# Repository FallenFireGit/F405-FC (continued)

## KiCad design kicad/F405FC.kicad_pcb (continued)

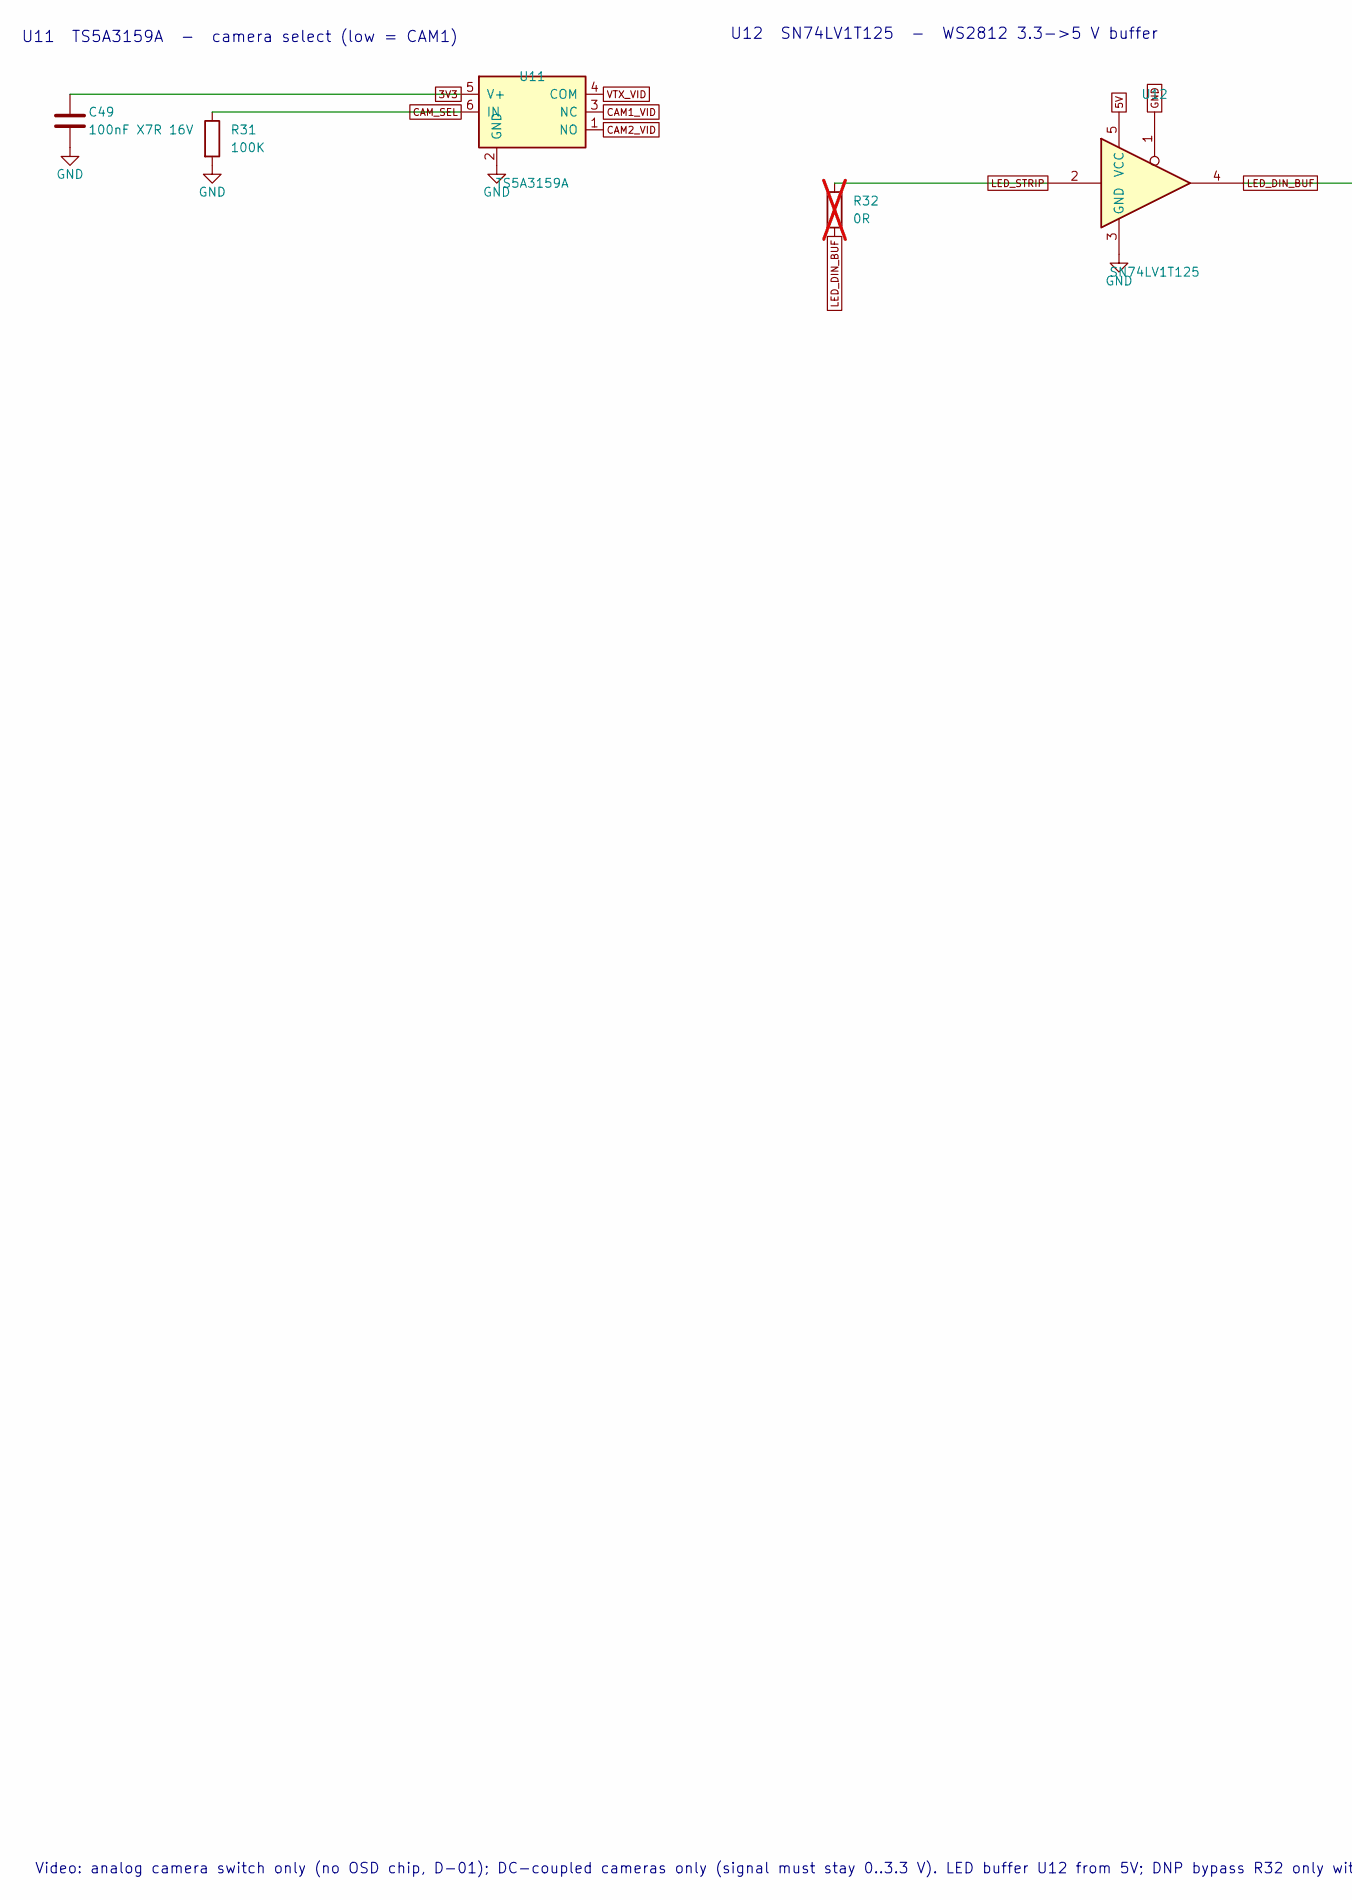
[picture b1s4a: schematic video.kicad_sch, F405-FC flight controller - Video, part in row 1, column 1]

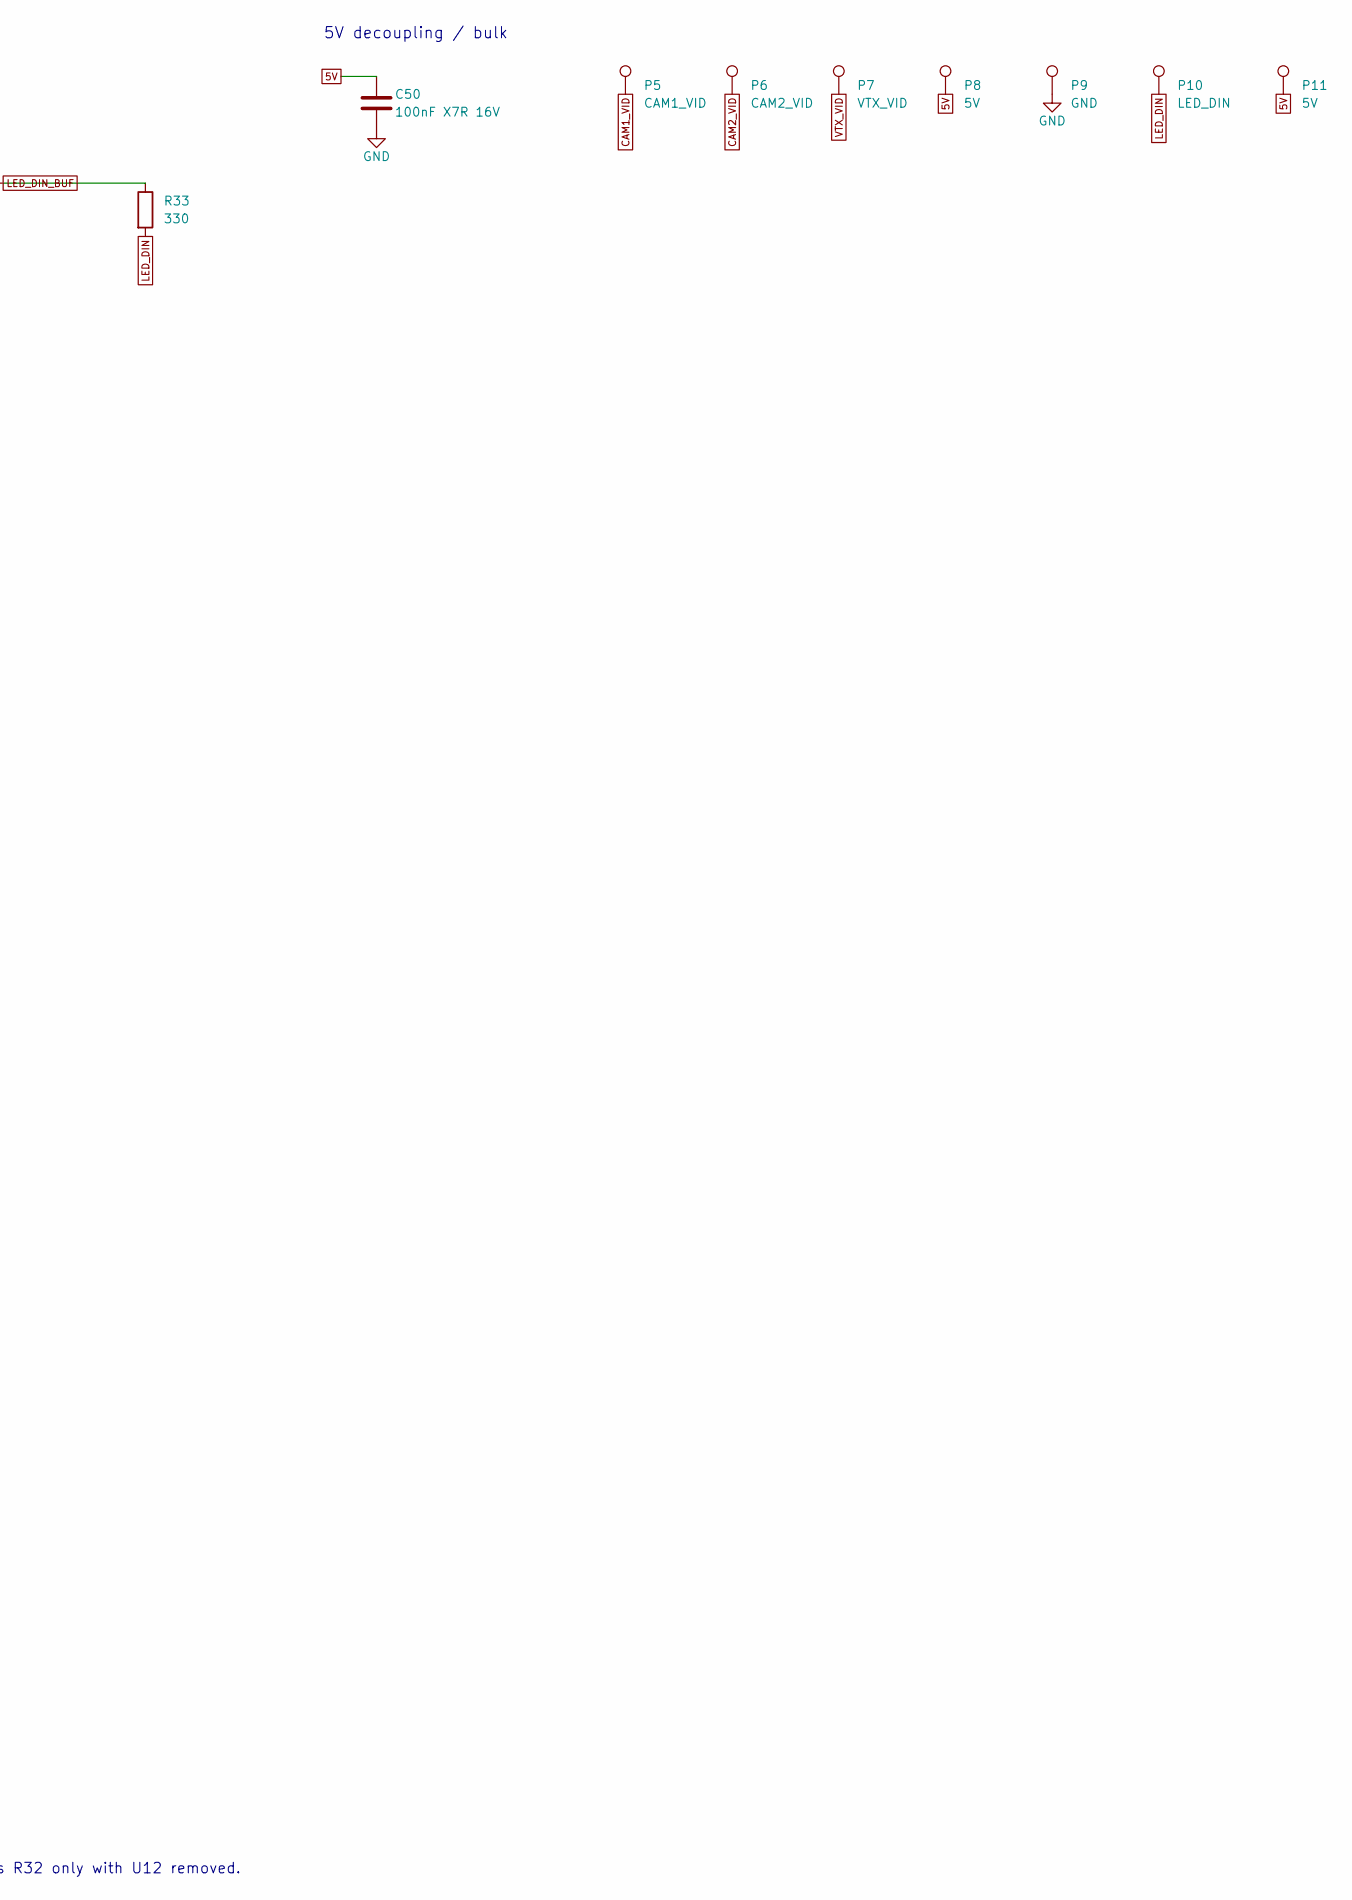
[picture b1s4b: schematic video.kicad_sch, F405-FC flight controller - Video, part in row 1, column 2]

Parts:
C49, C50: 100nF X7R 16V; C_0402_1005Metric; MPN CL05B104KO5NNNC; DigiKey 1276-1001-1-ND
P5: CAM1_VID; Pad_SMD_1.2x1.6mm; MPN n/a (PCB pad); DigiKey n/a (PCB pad)
P6: CAM2_VID; Pad_SMD_1.2x1.6mm; MPN n/a (PCB pad); DigiKey n/a (PCB pad)
P7: VTX_VID; Pad_SMD_1.2x1.6mm; MPN n/a (PCB pad); DigiKey n/a (PCB pad)
P8: 5V; Pad_SMD_1.2x1.6mm; MPN n/a (PCB pad); DigiKey n/a (PCB pad)
P9: GND; Pad_SMD_1.2x1.6mm; MPN n/a (PCB pad); DigiKey n/a (PCB pad)
P10: LED_DIN; Pad_SMD_1.2x1.6mm; MPN n/a (PCB pad); DigiKey n/a (PCB pad)
P11: 5V; Pad_SMD_1.5x2.0mm; MPN n/a (PCB pad); DigiKey n/a (PCB pad)
R31: 100K; R_0402_1005Metric; MPN RC0402FR-07100KL; DigiKey 311-100KLRCT-ND
R32: 0R; R_0402_1005Metric; MPN RC0402JR-070RL; DigiKey 311-0.0JRCT-ND; not fitted
R33: 330; R_0402_1005Metric; MPN RC0402FR-07330RL; DigiKey 311-330LRCT-ND
U11: TS5A3159A; SOT-23-6; MPN TS5A3159ADBVR; DigiKey 296-19265-1-ND
U12: SN74LV1T125; SOT-23-5; MPN SN74LV1T125DBVR; DigiKey 296-37172-1-ND

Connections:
3V3: C49.1, U11.5 (V+); also elsewhere on the board
5V: C50.1, P8.1, P11.1, U12.5 (VCC); also elsewhere on the board
CAM1_VID: P5.1, U11.3 (NC)
CAM2_VID: P6.1, U11.1 (NO)
CAM_SEL: R31.1, U11.6 (IN); also elsewhere on the board
GND: C49.2, C50.2, P9.1, R31.2, U11.2 (GND), U12.1, U12.3 (GND); also elsewhere on the board
LED_DIN: P10.1, R33.2
LED_DIN_BUF: R32.2, R33.1, U12.4
LED_STRIP: R32.1, U12.2; also elsewhere on the board
VTX_VID: P7.1, U11.4 (COM)

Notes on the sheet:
U11 TS5A3159A - camera select (low = CAM1)
U12 SN74LV1T125 - WS2812 3.3->5 V buffer
5V decoupling / bulk
Video: analog camera switch only (no OSD chip, D-01); DC-coupled cameras only (signal must stay 0..3.3 V). LED buffer U12 from 5V; DNP bypass R32 only with U12 removed.

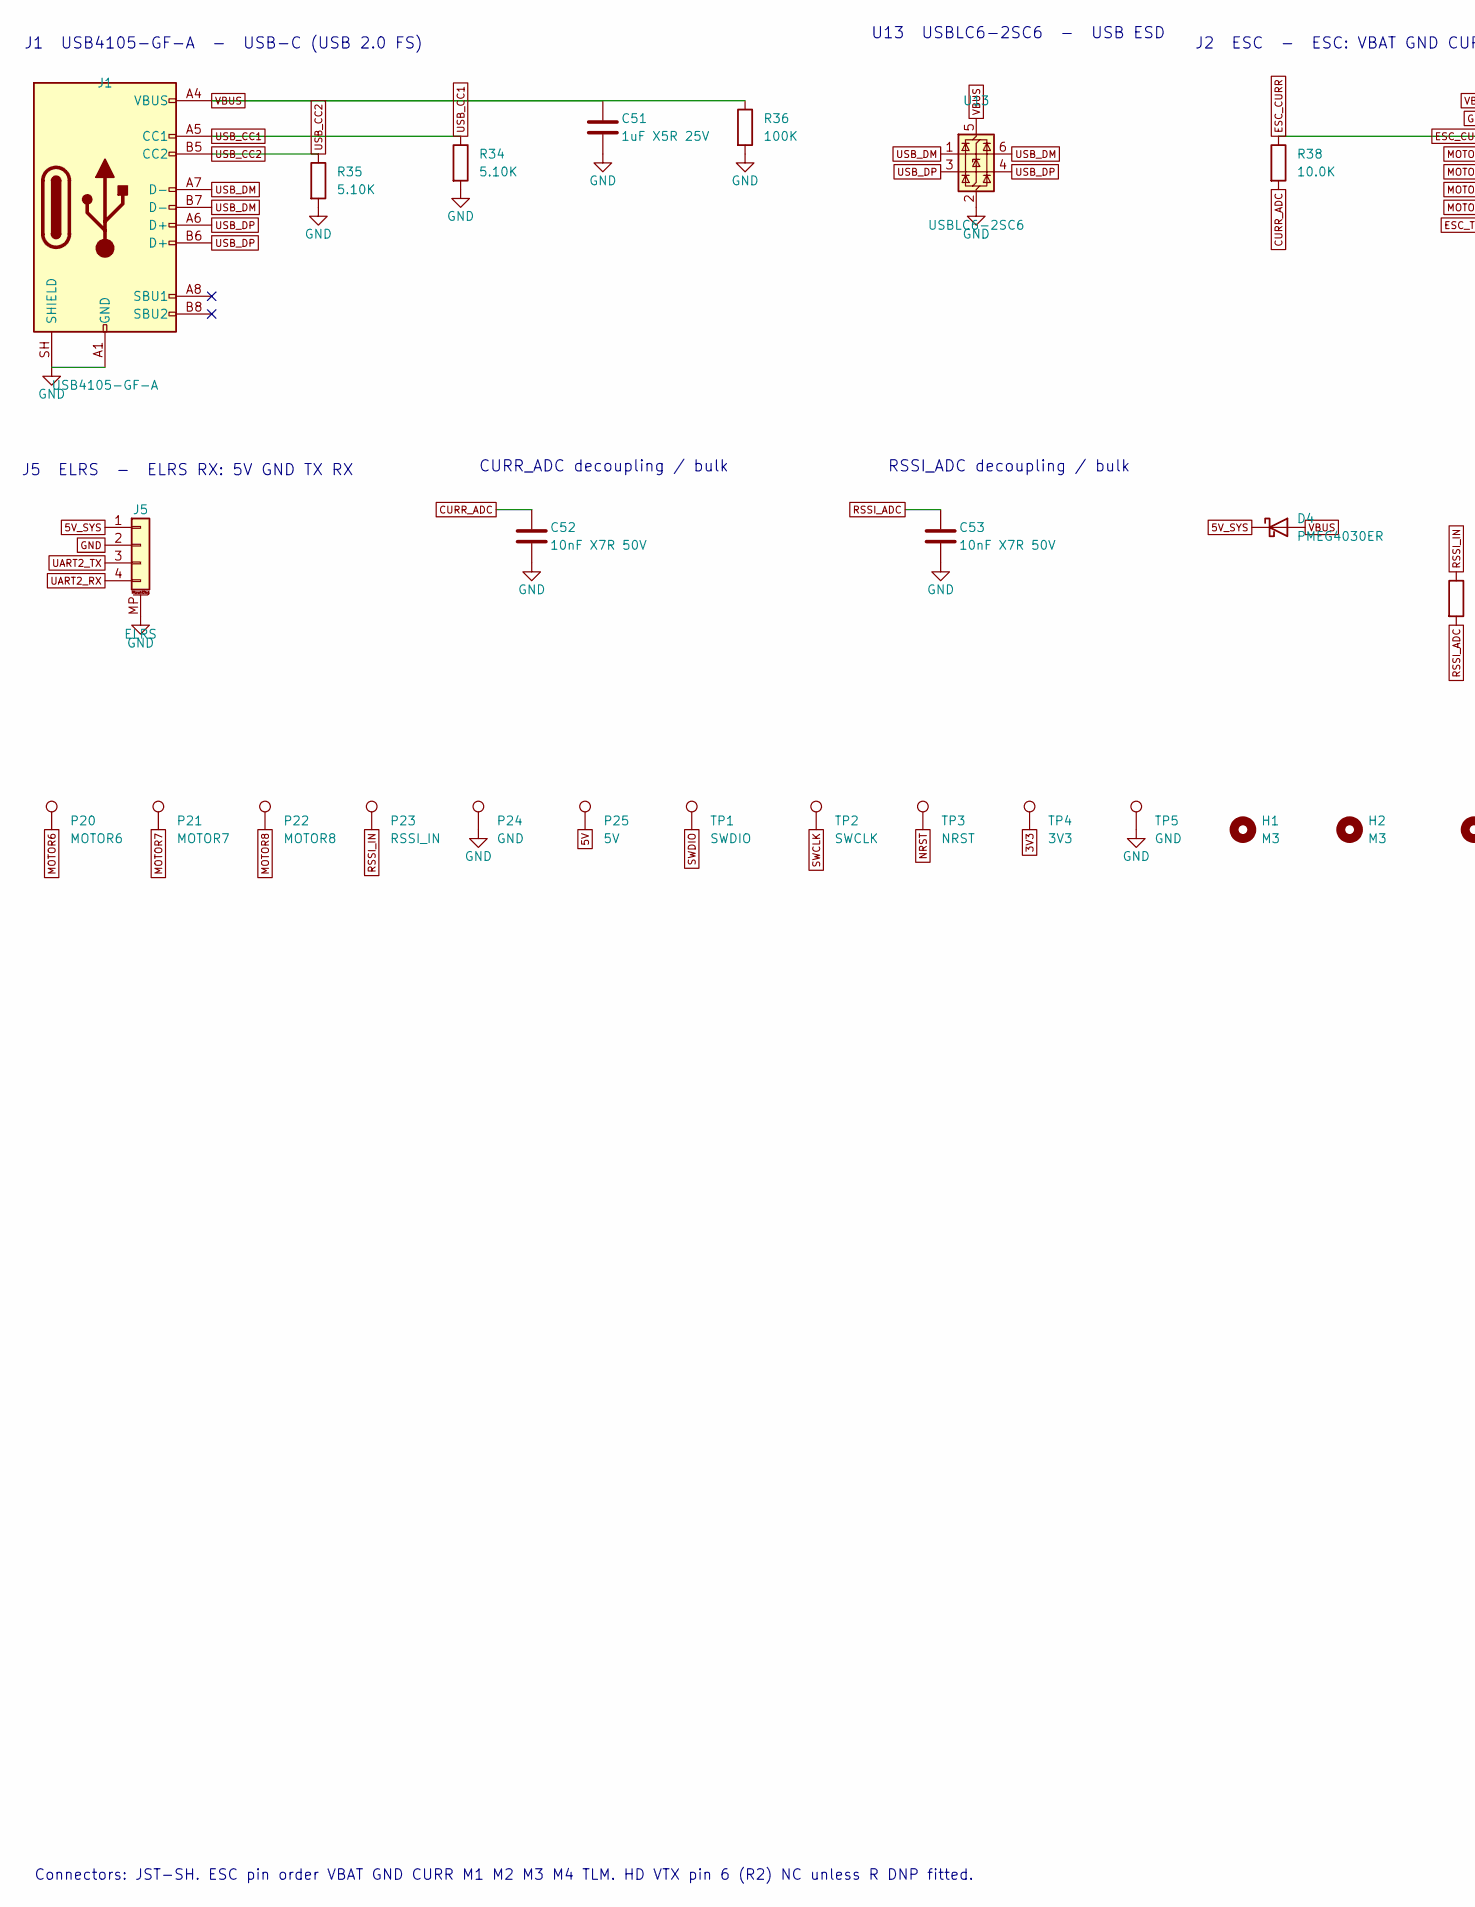
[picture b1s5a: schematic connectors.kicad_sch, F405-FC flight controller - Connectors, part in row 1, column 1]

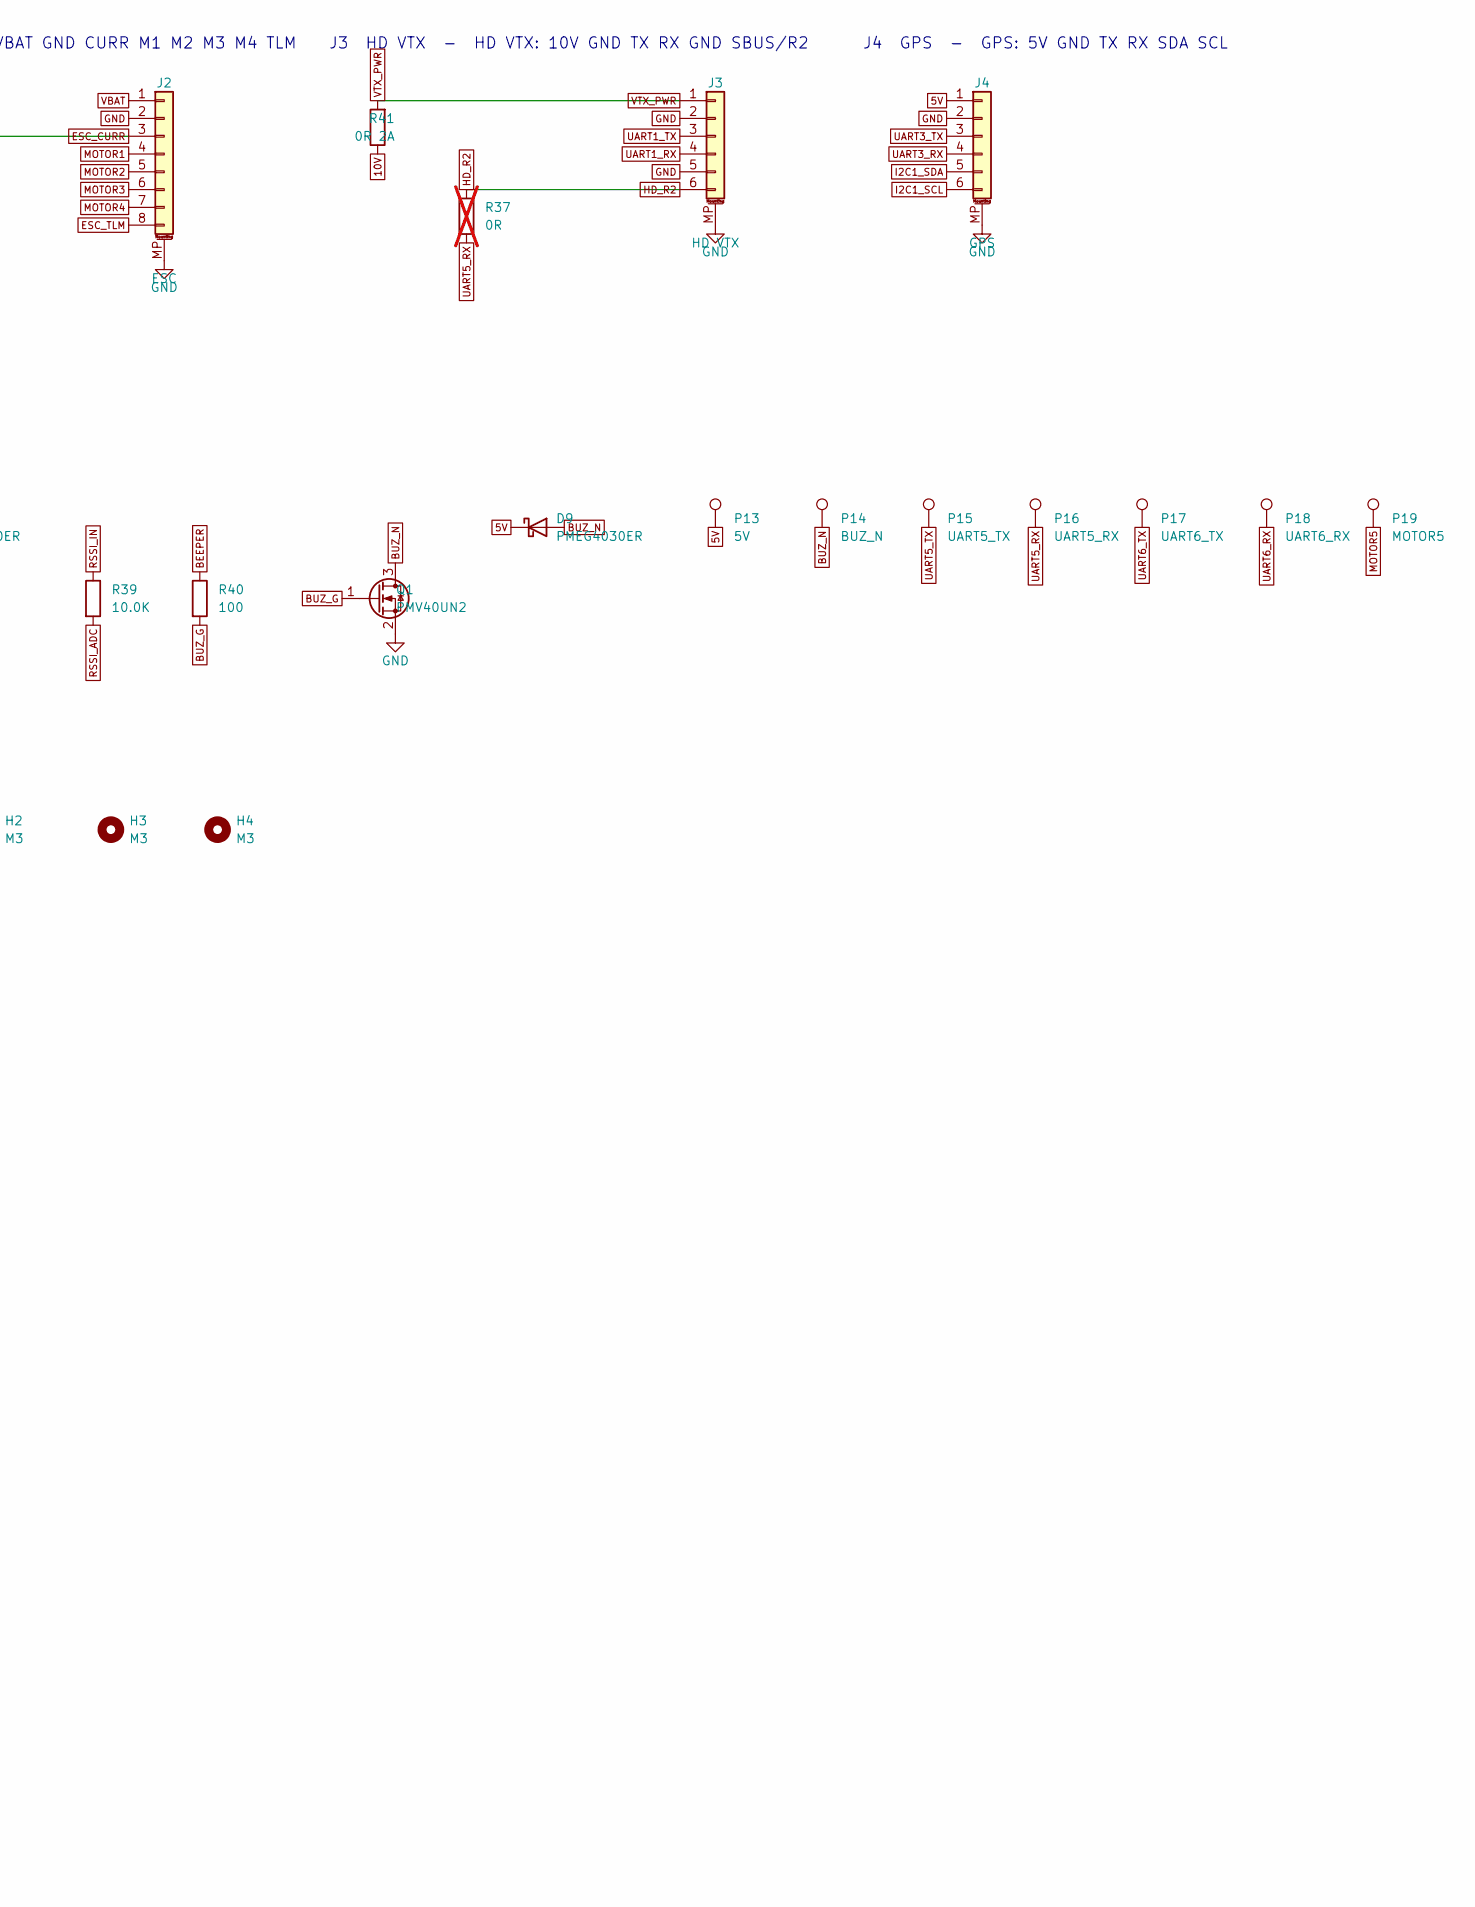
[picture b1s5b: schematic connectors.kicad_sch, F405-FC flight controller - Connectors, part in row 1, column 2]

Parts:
C51: 1uF X5R 25V; C_0603_1608Metric; MPN CL10A105KA8NNNC; DigiKey 1276-1102-1-ND (verify)
C52, C53: 10nF X7R 50V; C_0402_1005Metric; MPN CL05B103KB5NNNC; DigiKey 1276-1028-1-ND
D4, D9: PMEG4030ER; Nexperia_CFP3_SOD-123W; MPN PMEG4030ER,115; DigiKey 1727-5313-1-ND
H1, H2, H3, H4: M3; MountingHole_3.2mm_M3_Grommet4.6mm; MPN n/a (hole); DigiKey n/a (hole)
J1: USB4105-GF-A; USB_C_Receptacle_GCT_USB4105-xx-A_16P_TopMnt_Horizontal; MPN USB4105-GF-A; DigiKey 2073-USB4105-GF-ACT-ND
J2: ESC; JST_SH_SM08B-SRSS-TB_1x08-1MP_P1.00mm_Horizontal; MPN SM08B-SRSS-TB(LF)(SN); DigiKey 455-1808-1-ND
J3: HD VTX; JST_SH_SM06B-SRSS-TB_1x06-1MP_P1.00mm_Horizontal; MPN SM06B-SRSS-TB(LF)(SN); DigiKey 455-1806-1-ND
J4: GPS; JST_SH_SM06B-SRSS-TB_1x06-1MP_P1.00mm_Horizontal; MPN SM06B-SRSS-TB(LF)(SN); DigiKey 455-1806-1-ND
J5: ELRS; JST_SH_SM04B-SRSS-TB_1x04-1MP_P1.00mm_Horizontal; MPN SM04B-SRSS-TB(LF)(SN); DigiKey 455-1804-1-ND
P13, P25: 5V; Pad_SMD_1.2x1.6mm; MPN n/a (PCB pad); DigiKey n/a (PCB pad)
P14: BUZ_N; Pad_SMD_1.2x1.6mm; MPN n/a (PCB pad); DigiKey n/a (PCB pad)
P15: UART5_TX; Pad_SMD_1.2x1.6mm; MPN n/a (PCB pad); DigiKey n/a (PCB pad)
P16: UART5_RX; Pad_SMD_1.2x1.6mm; MPN n/a (PCB pad); DigiKey n/a (PCB pad)
P17: UART6_TX; Pad_SMD_1.2x1.6mm; MPN n/a (PCB pad); DigiKey n/a (PCB pad)
P18: UART6_RX; Pad_SMD_1.2x1.6mm; MPN n/a (PCB pad); DigiKey n/a (PCB pad)
P19: MOTOR5; Pad_SMD_1.2x1.6mm; MPN n/a (PCB pad); DigiKey n/a (PCB pad)
P20: MOTOR6; Pad_SMD_1.2x1.6mm; MPN n/a (PCB pad); DigiKey n/a (PCB pad)
P21: MOTOR7; Pad_SMD_1.2x1.6mm; MPN n/a (PCB pad); DigiKey n/a (PCB pad)
P22: MOTOR8; Pad_SMD_1.2x1.6mm; MPN n/a (PCB pad); DigiKey n/a (PCB pad)
P23: RSSI_IN; Pad_SMD_1.2x1.6mm; MPN n/a (PCB pad); DigiKey n/a (PCB pad)
P24: GND; Pad_SMD_1.2x1.6mm; MPN n/a (PCB pad); DigiKey n/a (PCB pad)
Q1: PMV40UN2; SOT-23; MPN PMV40UN2R; DigiKey 1727-1900-1-ND
R34, R35: 5.10K; R_0402_1005Metric; MPN RC0402FR-075K1L; DigiKey 311-5.10KLRCT-ND
R36: 100K; R_0402_1005Metric; MPN RC0402FR-07100KL; DigiKey 311-100KLRCT-ND
R37: 0R; R_0402_1005Metric; MPN RC0402JR-070RL; DigiKey 311-0.0JRCT-ND; not fitted
R38, R39: 10.0K; R_0402_1005Metric; MPN RC0402FR-0710KL; DigiKey 311-10.0KLRCT-ND
R40: 100; R_0402_1005Metric; MPN RC0402FR-07100RL; DigiKey 311-100LRCT-ND
R41: 0R 2A; R_0805_2012Metric; MPN RC0805JR-070RL; DigiKey 311-0.0ARCT-ND
TP1: SWDIO; TestPoint_Pad_D1.0mm; MPN n/a (test pad); DigiKey n/a (test pad)
TP2: SWCLK; TestPoint_Pad_D1.0mm; MPN n/a (test pad); DigiKey n/a (test pad)
TP3: NRST; TestPoint_Pad_D1.0mm; MPN n/a (test pad); DigiKey n/a (test pad)
TP4: 3V3; TestPoint_Pad_D1.0mm; MPN n/a (test pad); DigiKey n/a (test pad)
TP5: GND; TestPoint_Pad_D1.0mm; MPN n/a (test pad); DigiKey n/a (test pad)
U13: USBLC6-2SC6; SOT-23-6; MPN USBLC6-2SC6; DigiKey 497-5235-1-ND

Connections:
3V3: TP4.1; also elsewhere on the board
5V: D9.1 (K), J4.1, P13.1, P25.1; also elsewhere on the board
5V_SYS: D4.1 (K), J5.1; also elsewhere on the board
10V: R41.1; also elsewhere on the board
BEEPER: R40.1; also elsewhere on the board
BUZ_G: Q1.1 (G), R40.2
BUZ_N: D9.2 (A), P14.1, Q1.3 (D)
CURR_ADC: C52.1, R38.2; also elsewhere on the board
ESC_CURR: J2.3, R38.1
ESC_TLM: J2.8; also elsewhere on the board
GND: C51.2, C52.2, C53.2, J1.A1 (GND), J1.A12 (GND), J1.B1 (GND), J1.B12 (GND), J1.SH (SHIELD), J2.2, J2.MP (MountPin), J3.2, J3.5, J3.MP (MountPin), J4.2, J4.MP (MountPin), J5.2, J5.MP (MountPin), P24.1, Q1.2 (S), R34.2, R35.2, R36.2, TP5.1, U13.2 (GND); also elsewhere on the board
HD_R2: J3.6, R37.1
I2C1_SCL: J4.6; also elsewhere on the board
I2C1_SDA: J4.5; also elsewhere on the board
MOTOR1: J2.4; also elsewhere on the board
MOTOR2: J2.5; also elsewhere on the board
MOTOR3: J2.6; also elsewhere on the board
MOTOR4: J2.7; also elsewhere on the board
MOTOR5: P19.1; also elsewhere on the board
MOTOR6: P20.1; also elsewhere on the board
MOTOR7: P21.1; also elsewhere on the board
MOTOR8: P22.1; also elsewhere on the board
NRST: TP3.1; also elsewhere on the board
RSSI_ADC: C53.1, R39.2; also elsewhere on the board
RSSI_IN: P23.1, R39.1
SWCLK: TP2.1; also elsewhere on the board
SWDIO: TP1.1; also elsewhere on the board
UART1_RX: J3.4; also elsewhere on the board
UART1_TX: J3.3; also elsewhere on the board
UART2_RX: J5.4; also elsewhere on the board
UART2_TX: J5.3; also elsewhere on the board
UART3_RX: J4.4; also elsewhere on the board
UART3_TX: J4.3; also elsewhere on the board
UART5_RX: P16.1, R37.2; also elsewhere on the board
UART5_TX: P15.1; also elsewhere on the board
UART6_RX: P18.1; also elsewhere on the board
UART6_TX: P17.1; also elsewhere on the board
USB_CC1: J1.A5 (CC1), R34.1
USB_CC2: J1.B5 (CC2), R35.1
USB_DM: J1.A7 (D-), J1.B7 (D-), U13.1 (I/O1), U13.6 (I/O1); also elsewhere on the board
USB_DP: J1.A6 (D+), J1.B6 (D+), U13.3 (I/O2), U13.4 (I/O2); also elsewhere on the board
VBAT: J2.1; also elsewhere on the board
VBUS: C51.1, D4.2 (A), J1.A4 (VBUS), J1.A9 (VBUS), J1.B4 (VBUS), J1.B9 (VBUS), R36.1, U13.5 (VBUS)
VTX_PWR: J3.1, R41.2

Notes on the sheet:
J1 USB4105-GF-A - USB-C (USB 2.0 FS)
U13 USBLC6-2SC6 - USB ESD
J2 ESC - ESC: VBAT GND CURR M1 M2 M3 M4 TLM
J3 HD VTX - HD VTX: 10V GND TX RX GND SBUS/R2
J4 GPS - GPS: 5V GND TX RX SDA SCL
J5 ELRS - ELRS RX: 5V GND TX RX
CURR_ADC decoupling / bulk
RSSI_ADC decoupling / bulk
Connectors: JST-SH. ESC pin order VBAT GND CURR M1 M2 M3 M4 TLM. HD VTX pin 6 (R2) NC unless R DNP fitted.

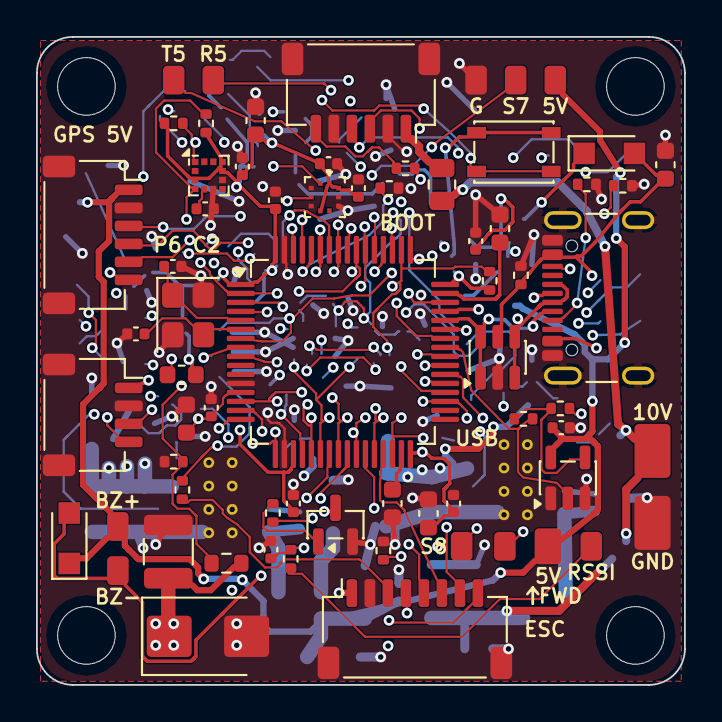
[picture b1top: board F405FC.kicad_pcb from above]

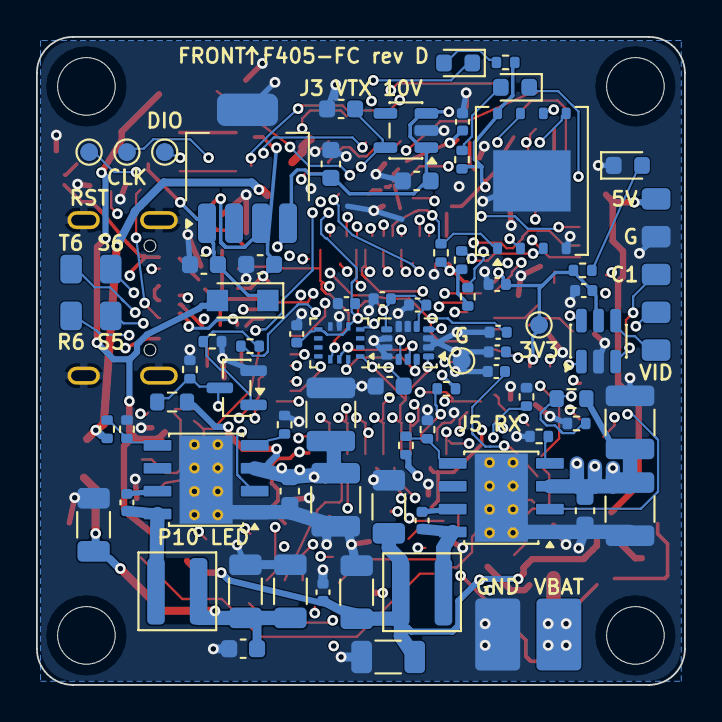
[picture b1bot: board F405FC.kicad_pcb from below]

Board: 6 copper layers, 36.0 x 36.0 mm, 154 parts (83 on the bottom side), 90 nets.

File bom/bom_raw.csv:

Qty per board,Refs,Value,MPN,Manufacturer,DigiKey PN,Footprint,Datasheet
20,C5 C9 C13 C24 C25 C26 C27 C28 C30 C32 C35 C38 C41 C42 C43 C44 C46 C48 C49 C50,100nF X7R 16V,CL05B104KO5NNNC,Samsung Electro-Mechanics,1276-1001-1-ND,C_0402_1005Metric,https://product.samsungsem.com/mlcc/CL05B104KO5NNNC.do
6,C6 C7 C8 C14 C15 C16,22uF X5R 25V,CL31A226KAHNNNE,Samsung Electro-Mechanics,1276-3047-1-ND,C_1206_3216Metric,https://product.samsungsem.com/mlcc/CL31A226KAHNNNE.do
4,C2 C3 C10 C11,4.7uF X7S 100V 2.0mm,C3225X7S2A475K200AB,TDK,445-6042-1-ND (verify: K200AB cut tape),C_1210_3225Metric,https://product.tdk.com/system/files/dam/doc/product/capacit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
4,C19 C22 C31 C51,1uF X5R 25V,CL10A105KA8NNNC,Samsung Electro-Mechanics,1276-1102-1-ND (verify),C_0603_1608Metric,https://product.samsungsem.com/mlcc/CL10A105KA8NNNC.do
3,C40 C52 C53,10nF X7R 50V,CL05B103KB5NNNC,Samsung Electro-Mechanics,1276-1028-1-ND,C_0402_1005Metric,https://product.samsungsem.com/mlcc/CL05B103KB5NNNC.do
3,C20 C33 C34,2.2uF X5R 16V,CL10A225KO8NNNC,Samsung Electro-Mechanics,1276-1040-1-ND,C_0603_1608Metric,https://product.samsungsem.com/mlcc/CL10A225KO8NNNC.do
3,C18 C29 C47,4.7uF X5R 16V,CL10A475KO8NNNC,Samsung Electro-Mechanics,1276-1784-1-ND,C_0603_1608Metric,https://product.samsungsem.com/mlcc/CL10A475KO8NNNC.do
3,C4 C12 C17,100nF X7R 100V,GRM188R72A104KA35D,Murata,490-3285-1-ND (verify),C_0603_1608Metric,https://search.murata.co.jp/Ceramy/image/img/A01X/G101/ENG/G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
2,C36 C37,8.2pF C0G 50V,C0402C829C5GACTU,KEMET,399-C0402C829C5GACTUCT-ND,C_0402_1005Metric,https://content.kemet.com/datasheets/KEM_C1003_C0G_SMD.pdf
2,C23 C39,2.2uF X7R 10V,CL10B225KP8NNNC,Samsung Electro-Mechanics,1276-1134-1-ND,C_0603_1608Metric,https://product.samsungsem.com/mlcc/CL10B225KP8NNNC.do
1,C45,220nF X5R 25V,CL05A224KA5NNNC,Samsung Electro-Mechanics,1276-1455-1-ND,C_0402_1005Metric,https://product.samsungsem.com/mlcc/CL05A224KA5NNNC.do
1,C1,10uF X7R 50V,CL32B106KBJNNNE,Samsung Electro-Mechanics,1276-3387-1-ND,C_1210_3225Metric,https://product.samsungsem.com/mlcc/CL32B106KBJNNNE.do
3,D5 D4 D9,PMEG4030ER,"PMEG4030ER,115",Nexperia,1727-5313-1-ND,Nexperia_CFP3_SOD-123W,https://assets.nexperia.com/documents/data-sheet/PMEG4030ER.pdf
1,D12,Green,LTST-C191KGKT,Lite-On,160-1446-1-ND,LED_0603_1608Metric,https://optoelectronics.liteon.com/upload/download/DS22-2000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
1,D10,Red,LTST-C191KRKT,Lite-On,160-1447-1-ND,LED_0603_1608Metric,https://optoelectronics.liteon.com/upload/download/DS22-2000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
1,D11,Blue,LTST-C191TBKT,Lite-On,160-1647-1-ND,LED_0603_1608Metric,https://optoelectronics.liteon.com/upload/download/DS22-2000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
1,D1,SMBJ26A,SMBJ26A,Littelfuse,SMBJ26ALFCT-ND,D_SMB,https://www.littelfuse.com/assetdocs/tvs-diodes-smbj-series-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
1,FB1,600R@100MHz,BLM18KG601SN1D,Murata,490-5258-1-ND,L_0603_1608Metric,https://www.murata.com/en-us/products/productdata/8796740616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
2,J3 J4,HD VTX,SM06B-SRSS-TB(LF)(SN),JST,455-1806-1-ND,JST_SH_SM06B-SRSS-TB_1x06-1MP_P1.00mm_Horizontal,https://www.jst-mfg.com/product/pdf/eng/eSH.pdf
1,J5,ELRS,SM04B-SRSS-TB(LF)(SN),JST,455-1804-1-ND,JST_SH_SM04B-SRSS-TB_1x04-1MP_P1.00mm_Horizontal,https://www.jst-mfg.com/product/pdf/eng/eSH.pdf
1,J2,ESC,SM08B-SRSS-TB(LF)(SN),JST,455-1808-1-ND,JST_SH_SM08B-SRSS-TB_1x08-1MP_P1.00mm_Horizontal,https://www.jst-mfg.com/product/pdf/eng/eSH.pdf
1,J1,USB4105-GF-A,USB4105-GF-A,GCT,2073-USB4105-GF-ACT-ND,USB_C_Receptacle_GCT_USB4105-xx-A_16P_TopMnt_Horizontal,https://gct.co/files/drawings/usb4105.pdf
2,L1 L2,5.6uH,78438356056,Würth Elektronik,732-11317-1-ND,L_Wuerth_MAPI-4020,https://www.we-online.com/components/products/datasheet/7843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
1,Q2,NX7002AK,"NX7002AK,215",Nexperia,1727-1289-1-ND,SOT-23,https://assets.nexperia.com/documents/data-sheet/NX7002AK.pdf
1,Q1,PMV40UN2,PMV40UN2R,Nexperia,1727-1900-1-ND,SOT-23,https://assets.nexperia.com/documents/data-sheet/PMV40UN2.pdf
9,R16 R17 R18 R19 R20 R29 R30 R38 R39,10.0K,RC0402FR-0710KL,Yageo,311-10.0KLRCT-ND,R_0402_1005Metric,https://www.yageo.com/upload/media/product/productsearch/dat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
7,R2 R4 R7 R9 R12 R31 R36,100K,RC0402FR-07100KL,Yageo,311-100KLRCT-ND,R_0402_1005Metric,https://www.yageo.com/upload/media/product/productsearch/dat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
4,R11 R13 R15 R28,1.00K,RC0402FR-071KL,Yageo,311-1.00KLRCT-ND,R_0402_1005Metric,https://www.yageo.com/upload/media/product/productsearch/dat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
2,R3 R8,34.8K,ERJ-2RKF3482X,Panasonic,P34.8KLCT-ND,R_0402_1005Metric,https://industrial.panasonic.com/cdbs/www-data/pdf/RDA0000/A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
2,R25 R26,2.20K,RC0402FR-072K2L,Yageo,311-2.20KLRCT-ND,R_0402_1005Metric,https://www.yageo.com/upload/media/product/productsearch/dat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
2,R27 R33,330,RC0402FR-07330RL,Yageo,311-330LRCT-ND,R_0402_1005Metric,https://www.yageo.com/upload/media/product/productsearch/dat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
2,R34 R35,5.10K,RC0402FR-075K1L,Yageo,311-5.10KLRCT-ND,R_0402_1005Metric,https://www.yageo.com/upload/media/product/productsearch/dat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
2,R1 R6,301K,RC0603FR-07301KL,Yageo,311-301KHRCT-ND,R_0603_1608Metric,https://www.yageo.com/upload/media/product/productsearch/dat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
1,R5,24.3K,ERJ-2RKF2432X,Panasonic,P24.3KLCT-ND,R_0402_1005Metric,https://industrial.panasonic.com/cdbs/www-data/pdf/RDA0000/A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
1,R40,100,RC0402FR-07100RL,Yageo,311-100LRCT-ND,R_0402_1005Metric,https://www.yageo.com/upload/media/product/productsearch/dat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
1,R10,11.0K,RC0402FR-0711KL,Yageo,311-11.0KLRCT-ND,R_0402_1005Metric,https://www.yageo.com/upload/media/product/productsearch/dat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
1,R14,10.0K,RC0603FR-0710KL,Yageo,311-10.0KHRCT-ND,R_0603_1608Metric,https://www.yageo.com/upload/media/product/productsearch/dat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
1,R41,0R 2A,RC0805JR-070RL,Yageo,311-0.0ARCT-ND,R_0805_2012Metric,https://www.yageo.com/upload/media/product/productsearch/dat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
1,SW1,BOOT,PTS810 SJM 250 SMTR LFS,C&K,CKN10502CT-ND,SW_SPST_PTS810,https://www.ckswitches.com/media/1476/pts810.pdf
2,U1 U2,LMR38020FSDDAR,LMR38020FSDDAR,Texas Instruments,296-LMR38020FSDDARCT-ND (verify),TI_HSOIC-8-1EP_3.9x4.9mm_P1.27mm_EP2.71x3.4mm_DDA,https://www.ti.com/lit/ds/symlink/lmr38020.pdf
1,U7,BMI270,BMI270,Bosch Sensortec,828-1091-1-ND,Bosch_LGA-14_3x2.5mm_P0.5mm_BMI270,https://www.bosch-sensortec.com/media/boschsensortec/downloa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
1,U8,BMP390,BMP390,Bosch Sensortec,828-BMP390CT-ND,Bosch_LGA-10_2x2mm_P0.5mm_BMP390,https://www.bosch-sensortec.com/media/boschsensortec/downloa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
1,U6,ICM-42688-P,ICM-42688-P,TDK InvenSense,1428-ICM-42688-PCT-ND,LGA-14_3x2.5mm_P0.5mm_LayoutBorder3x4y,https://invensense.tdk.com/wp-content/uploads/2020/04/ds-000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
1,U9,IIS2MDC,IIS2MDCTR,STMicroelectronics,497-17728-1-ND,LGA-12_2x2mm_P0.5mm,https://www.st.com/resource/en/datasheet/iis2mdc.pdf
1,U4,LP38692MP-3.3,LP38692MP-3.3/NOPB,Texas Instruments,LP38692MP-3.3/NOPBCT-ND,SOT-223-5,https://www.ti.com/lit/ds/symlink/lp38692.pdf
1,U5,LP5907MFX-3.3,LP5907MFX-3.3/NOPB,Texas Instruments,296-38557-1-ND,SOT-23-5,https://www.ti.com/lit/ds/symlink/lp5907.pdf
1,U12,SN74LV1T125,SN74LV1T125DBVR,Texas Instruments,296-37172-1-ND,SOT-23-5,https://www.ti.com/lit/ds/symlink/sn74lv1t125.pdf
1,U3,STM32F405RGT6,STM32F405RGT6,STMicroelectronics,497-11767-ND,LQFP-64_10x10mm_P0.5mm,https://www.st.com/resource/en/datasheet/stm32f405rg.pdf
1,U11,TS5A3159A,TS5A3159ADBVR,Texas Instruments,296-19265-1-ND,SOT-23-6,https://www.ti.com/lit/ds/symlink/ts5a3159a.pdf
1,U13,USBLC6-2SC6,USBLC6-2SC6,STMicroelectronics,497-5235-1-ND,SOT-23-6,https://www.st.com/resource/en/datasheet/usblc6-2.pdf
1,U10,W25N01GV,W25N01GVZEIG TR,Winbond,256-W25N01GVZEIGTRCT-ND,WSON-8-1EP_8x6mm_P1.27mm_EP3.4x4.3mm,https://www.winbond.com/resource-files/w25n01gv%20revl%20050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
1,Y1,8MHz,ECS-80-8-33-JEN-TR3,ECS Inc.,50-ECS-80-8-33-JEN-TR3CT-ND,Crystal_SMD_3225-4Pin_3.2x2.5mm,https://ecsxtal.com/store/pdf/ECX-32.pdf

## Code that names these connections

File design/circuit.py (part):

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# MCU sheet
# ============================================================================================
mcu_conn = {
    "VBAT": "3V3", "PC13": "CAM_SEL", "PC14": "GYRO2_INT", "PC15": "VTX_PWR_EN", "PH0": "HSE_IN", "PH1": "HSE_OUT",
    "NRST": "NRST", "PC0": "VBAT_ADC", "PC1": "CURR_ADC", "PC2": None, "PC3": None, "VSSA": "GND", "VDDA": "3V3A",
    "PA0": "MOTOR8", "PA1": "ESC_TLM", "PA2": "UART2_TX", "PA3": "UART2_RX", "VSS": "GND", "VDD": "3V3",
    "PA4": "GYRO1_CS", "PA5": "SPI1_SCK", "PA6": "SPI1_MISO", "PA7": "SPI1_MOSI", "PC4": "GYRO1_INT", "PC5": "RSSI_ADC",
    "PB0": "MOTOR1", "PB1": "MOTOR2", "PB2": "BEEPER", "PB10": "MOTOR3", "PB11": "MOTOR4", "VCAP_1": "VCAP1",
    "PB12": None, "PB13": None, "PB14": "STATUS_LED_BLUE", "PB15": "STATUS_LED_GREEN", "PC6": "UART6_TX",
    "PC7": "UART6_RX", "PC8": "MOTOR5", "PC9": "MOTOR6", "PA8": "LED_STRIP", "PA9": "UART1_TX", "PA10": "UART1_RX",
    "PA11": "USB_DM", "PA12": "USB_DP", "PA13": "SWDIO", "VCAP_2": "VCAP2", "PA14": "SWCLK", "PA15": "GYRO2_CS",
    "PC10": "UART3_TX", "PC11": "UART3_RX", "PC12": "UART5_TX", "PD2": "UART5_RX", "PB3": "SPI3_SCK",
    "PB4": "SPI3_MISO", "PB5": "SPI3_MOSI", "PB6": "FLASH_CS", "PB7": "MOTOR7", "BOOT0": "BOOT0", "PB8": "I2C1_SCL",
    "PB9": "I2C1_SDA",
}
part(MCU, "U3", "MCU_ST_STM32F4:STM32F405RGTx", "STM32F405RGT6", FP["STM32"], mcu_conn,
     "STM32F405RGT6", "STMicroelectronics", "497-11767-ND", "https://www.st.com/resource/en/datasheet/stm32f405rg.pdf",
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part(MCU, "SW1", "Switch:SW_Push", "BOOT", FP["SW"], {"1": "3V3", "2": "BOOT0"},
     "PTS810 SJM 250 SMTR LFS", "C&K", "CKN10502CT-ND",
     "https://www.ckswitches.com/media/1476/pts810.pdf", desc="BOOT button (BOOT0 high)")
R(MCU, "R10k", "BEEPER", "GND")  # PB2 = BOOT1 strap + beeper FET gate pulldown
part(MCU, "Y1", "Device:Crystal_GND24", "8MHz", FP["XTAL"], {"1": "HSE_IN", "3": "HSE_OUT", "2": "GND", "4": "GND"},
     "ECS-80-8-33-JEN-TR3", "ECS Inc.", "50-ECS-80-8-33-JEN-TR3CT-ND",
     "https://ecsxtal.com/store/pdf/ECX-32.pdf", desc="8 MHz HSE crystal, CL 8 pF")
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    R(CON, "R10k", src, adc)
    C(CON, "C10n", adc)

# Buzzer driver: PMV40UN2, gate 100R from PB2 node (10k BOOT1 pulldown on MCU sheet)
R(CON, "R100", "BEEPER", "BUZ_G")
part(CON, "Q1", "Transistor_FET:2N7002", "PMV40UN2", FP["SOT23"], {"G": "BUZ_G", "S": "GND", "D": "BUZ_N"},
     "PMV40UN2R", "Nexperia", "1727-1900-1-ND", "https://assets.nexperia.com/documents/data-sheet/PMV40UN2.pdf",
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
